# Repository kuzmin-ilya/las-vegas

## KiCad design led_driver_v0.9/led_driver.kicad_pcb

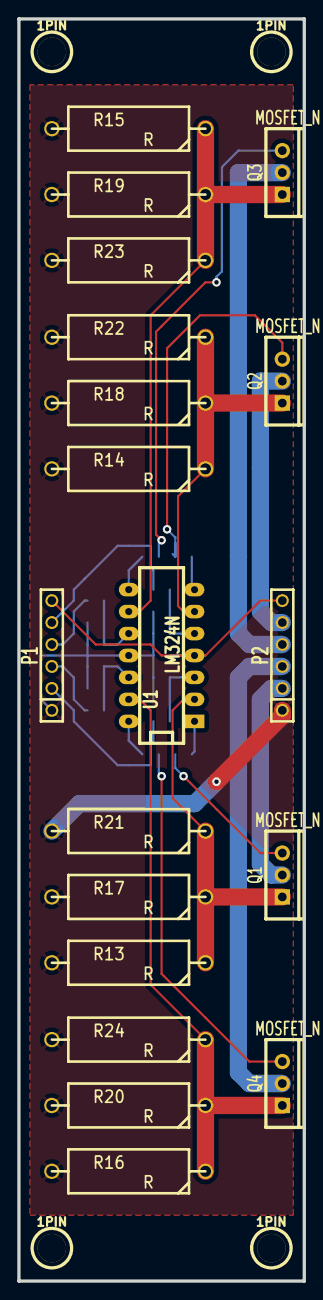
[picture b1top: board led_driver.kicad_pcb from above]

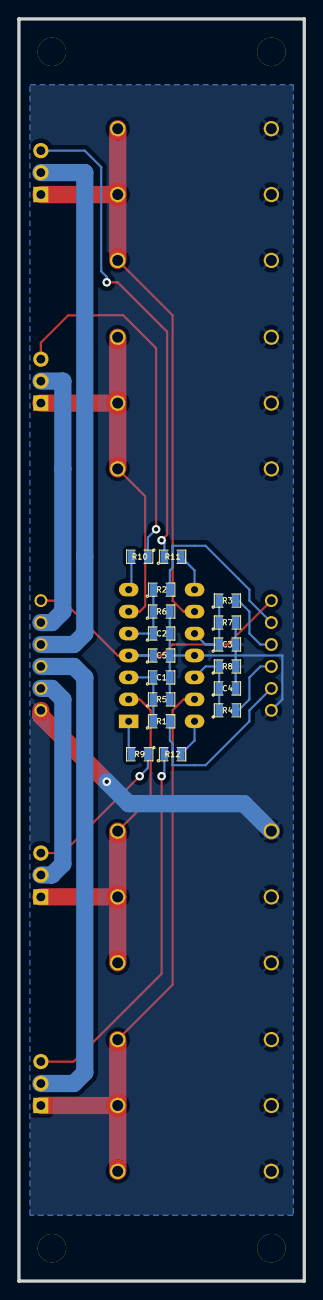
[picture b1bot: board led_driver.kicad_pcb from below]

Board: 2 copper layers, 33.0 x 146.0 mm, 40 parts (17 on the bottom side), 26 nets.

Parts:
1PIN, 1PIN#2, 1PIN#3, 1PIN#4: P***; 1pin
C1, C2, C3, C4, C5: C; SM0805
P1, P2: CONN_6; SIL-6
Q1, Q2, Q3, Q4: MOSFET_N; TO220_VERT
R1, R2, R3, R4, R5, R6, R7, R8, R9, R10, R11, R12: R; SM0805
R13, R14, R15, R16, R17, R18, R19, R20, R21, R22, R23, R24: R; R7
U1: LM324N; DIP-14__300_ELL

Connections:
+5V: C5.1, P1.6, P2.6, U1.4
GND: C1.2, C2.2, C3.2, C4.2, C5.2, P1.1, P2.1, R5.2, R6.2, R7.2, R8.2, R13.2, R14.2, R15.2, R16.2, R17.2, R18.2, R19.2, R20.2, R21.2, R22.2, R23.2, R24.2, U1.11
unnamed: C3.1, R3.1, R7.1, U1.10
unnamed: P1.4, R3.2
unnamed: C4.1, R4.1, R8.1, U1.12
unnamed: P1.3, R4.2
unnamed: P1.5, R2.2
unnamed: Q3.g, R11.1
unnamed: R11.2, U1.8
unnamed: Q3.s, R15.1, R19.1, R23.1, U1.9
unnamed: P1.2, R1.2
unnamed: C1.1, R1.1, R5.1, U1.3
unnamed: Q1.g, R9.1
unnamed: Q1.s, R13.1, R17.1, R21.1, U1.2
unnamed: R9.2, U1.1
unnamed: P2.3, Q4.d
unnamed: Q4.g, R12.1
unnamed: Q4.s, R16.1, R20.1, R24.1, U1.13
unnamed: R12.2, U1.14
unnamed: Q2.g, R10.1
unnamed: R10.2, U1.7
unnamed: Q2.s, R14.1, R18.1, R22.1, U1.6
unnamed: C2.1, R2.1, R6.1, U1.5
unnamed: P2.2, Q1.d
unnamed: P2.4, Q3.d
unnamed: P2.5, Q2.d

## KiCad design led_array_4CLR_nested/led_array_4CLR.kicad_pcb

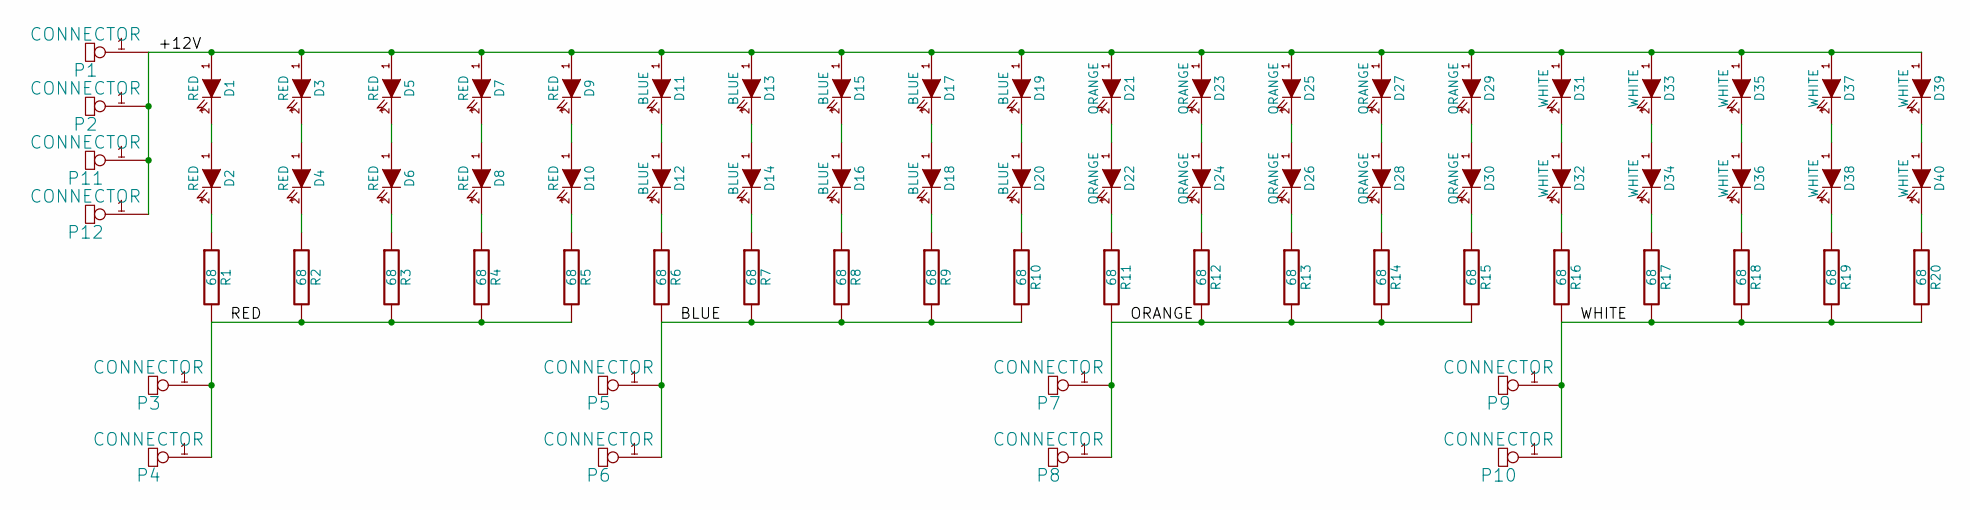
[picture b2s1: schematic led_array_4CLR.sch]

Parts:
D1, D2, D3, D4, D5, D6, D7, D8, D9, D10: RED; LED-5MM
D11, D12, D13, D14, D15, D16, D17, D18, D19, D20: BLUE; LED-5MM
D21, D22, D23, D24, D25, D26, D27, D28, D29, D30: ORANGE; LED-5MM
D31, D32, D33, D34, D35, D36, D37, D38, D39, D40: WHITE; LED-5MM
P1, P2, P3, P4, P5, P6, P7, P8, P9, P10, P11, P12: CONNECTOR
R1, R2, R3, R4, R5, R6, R7, R8, R9, R10, R11, R12, R13, R14, R15, R16, R17, R18, R19, R20: 68; R5

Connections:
/+12V: D1.1 (A), D3.1 (A), D5.1 (A), D7.1 (A), D9.1 (A), D11.1 (A), D13.1 (A), D15.1 (A), D17.1 (A), D19.1 (A), D21.1 (A), D23.1 (A), D25.1 (A), D27.1 (A), D29.1 (A), D31.1 (A), D33.1 (A), D35.1 (A), D37.1 (A), D39.1 (A), P1.1, P2.1, P11.1, P12.1
/BLUE: P5.1, P6.1, R6.2, R7.2, R8.2, R9.2, R10.2
/ORANGE: P7.1, P8.1, R11.2, R12.2, R13.2, R14.2, R15.2
/RED: P3.1, P4.1, R1.2, R2.2, R3.2, R4.2, R5.2
/WHITE: P9.1, P10.1, R16.2, R17.2, R18.2, R19.2, R20.2
unnamed: D23.2 (K), D24.1 (A)
unnamed: D24.2 (K), R12.1
unnamed: D22.2 (K), R11.1
unnamed: D21.2 (K), D22.1 (A)
unnamed: D26.2 (K), R13.1
unnamed: D25.2 (K), D26.1 (A)
unnamed: D27.2 (K), D28.1 (A)
unnamed: D28.2 (K), R14.1
unnamed: D30.2 (K), R15.1
unnamed: D29.2 (K), D30.1 (A)
unnamed: D19.2 (K), D20.1 (A)
unnamed: D9.2 (K), D10.1 (A)
unnamed: D7.2 (K), D8.1 (A)
unnamed: D8.2 (K), R4.1
unnamed: D17.2 (K), D18.1 (A)
unnamed: D18.2 (K), R9.1
unnamed: D20.2 (K), R10.1
unnamed: D10.2 (K), R5.1
unnamed: D34.2 (K), R17.1
unnamed: D33.2 (K), D34.1 (A)
unnamed: D31.2 (K), D32.1 (A)
unnamed: D32.2 (K), R16.1
unnamed: D35.2 (K), D36.1 (A)
unnamed: D36.2 (K), R18.1
unnamed: D37.2 (K), D38.1 (A)
unnamed: D38.2 (K), R19.1
unnamed: D39.2 (K), D40.1 (A)
unnamed: D40.2 (K), R20.1
unnamed: D13.2 (K), D14.1 (A)
unnamed: D14.2 (K), R7.1
unnamed: D12.2 (K), R6.1
unnamed: D11.2 (K), D12.1 (A)
unnamed: D16.2 (K), R8.1
unnamed: D15.2 (K), D16.1 (A)
unnamed: D5.2 (K), D6.1 (A)
unnamed: D6.2 (K), R3.1
unnamed: D1.2 (K), D2.1 (A)
unnamed: D2.2 (K), R1.1
unnamed: D4.2 (K), R2.1
unnamed: D3.2 (K), D4.1 (A)

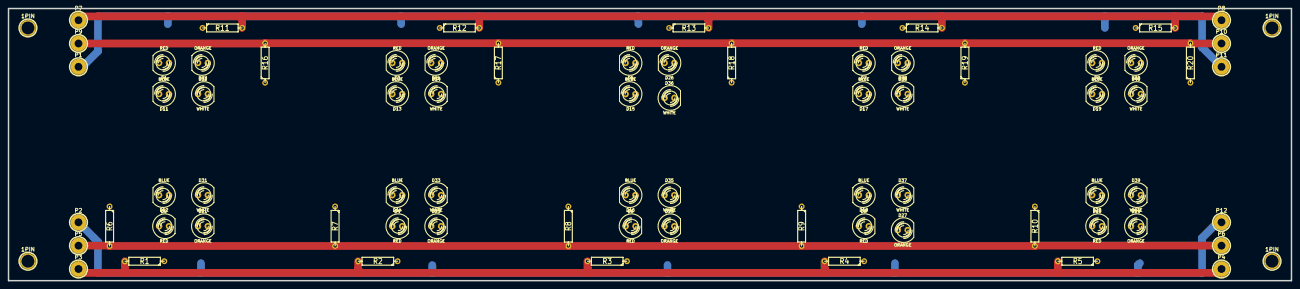
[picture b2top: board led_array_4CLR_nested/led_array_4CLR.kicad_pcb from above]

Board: 2 copper layers, 330.0 x 70.0 mm, 76 parts (0 on the bottom side), 45 nets.

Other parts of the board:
1PIN, 1PIN#2, 1PIN#3, 1PIN#4: P***; 1pin

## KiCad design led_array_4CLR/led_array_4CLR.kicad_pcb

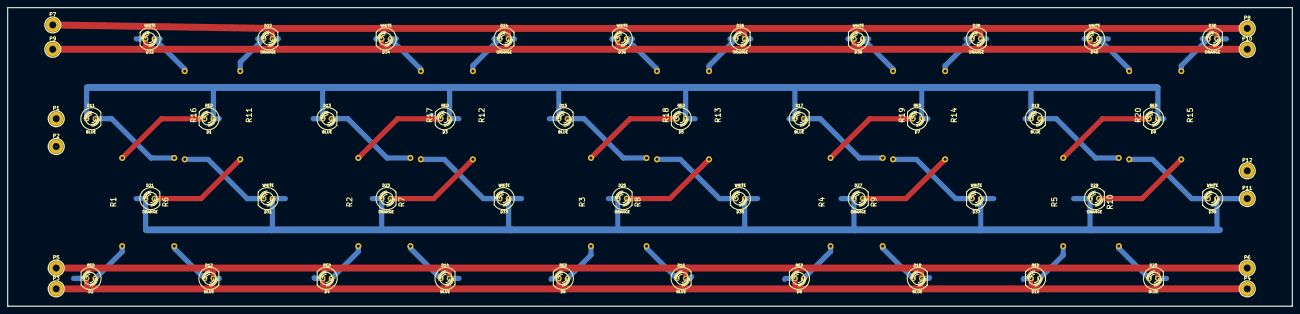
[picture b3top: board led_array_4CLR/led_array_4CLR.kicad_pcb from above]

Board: 2 copper layers, 370.0 x 86.0 mm, 72 parts (0 on the bottom side), 45 nets.

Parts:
D1, D2, D3, D4, D5, D6, D7, D8, D9, D10: RED; LED-5MM
D11, D12, D13, D14, D15, D16, D17, D18, D19, D20: BLUE; LED-5MM
D21, D22, D23, D24, D25, D26, D27, D28, D29, D30: ORANGE; LED-5MM
D31, D32, D33, D34, D35, D36, D37, D38, D39, D40: WHITE; LED-5MM
P1, P2, P3, P4, P5, P6, P7, P8, P9, P10, P11, P12: CONNECTOR; 1pin
R1, R2, R3, R4, R5, R6, R7, R8, R9, R10, R11, R12, R13, R14, R15, R16, R17, R18, R19, R20: 68; temp10

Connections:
/+12V: D1.1, D3.1, D5.1, D7.1, D9.1, D11.1, D13.1, D15.1, D17.1, D19.1, D21.1, D23.1, D25.1, D27.1, D29.1, D31.1, D33.1, D35.1, D37.1, D39.1, P1.1, P2.1, P11.1, P12.1
/BLUE: D12.2, D14.2, D16.2, D18.2, D20.2, P5.1, P6.1
/ORANGE: D22.2, D24.2, D26.2, D28.2, D30.2, P7.1, P8.1
/RED: D2.2, D4.2, D6.2, D8.2, D10.2, P3.1, P4.1
/WHITE: D32.2, D34.2, D36.2, D38.2, D40.2, P9.1, P10.1
unnamed: D24.1, R12.2
unnamed: D23.2, R12.1
unnamed: D21.2, R11.1
unnamed: D22.1, R11.2
unnamed: D25.2, R13.1
unnamed: D26.1, R13.2
unnamed: D28.1, R14.2
unnamed: D27.2, R14.1
unnamed: D29.2, R15.1
unnamed: D30.1, R15.2
unnamed: D20.1, R10.2
unnamed: D10.1, R5.2
unnamed: D7.2, R4.1
unnamed: D8.1, R4.2
unnamed: D18.1, R9.2
unnamed: D17.2, R9.1
unnamed: D19.2, R10.1
unnamed: D9.2, R5.1
unnamed: D34.1, R17.2
unnamed: D33.2, R17.1
unnamed: D31.2, R16.1
unnamed: D32.1, R16.2
unnamed: D35.2, R18.1
unnamed: D36.1, R18.2
unnamed: D38.1, R19.2
unnamed: D40.1, R20.2
unnamed: D37.2, R19.1
unnamed: D39.2, R20.1
unnamed: D14.1, R7.2
unnamed: D13.2, R7.1
unnamed: D11.2, R6.1
unnamed: D12.1, R6.2
unnamed: D15.2, R8.1
unnamed: D16.1, R8.2
unnamed: D6.1, R3.2
unnamed: D5.2, R3.1
unnamed: D2.1, R1.2
unnamed: D1.2, R1.1
unnamed: D3.2, R2.1
unnamed: D4.1, R2.2
